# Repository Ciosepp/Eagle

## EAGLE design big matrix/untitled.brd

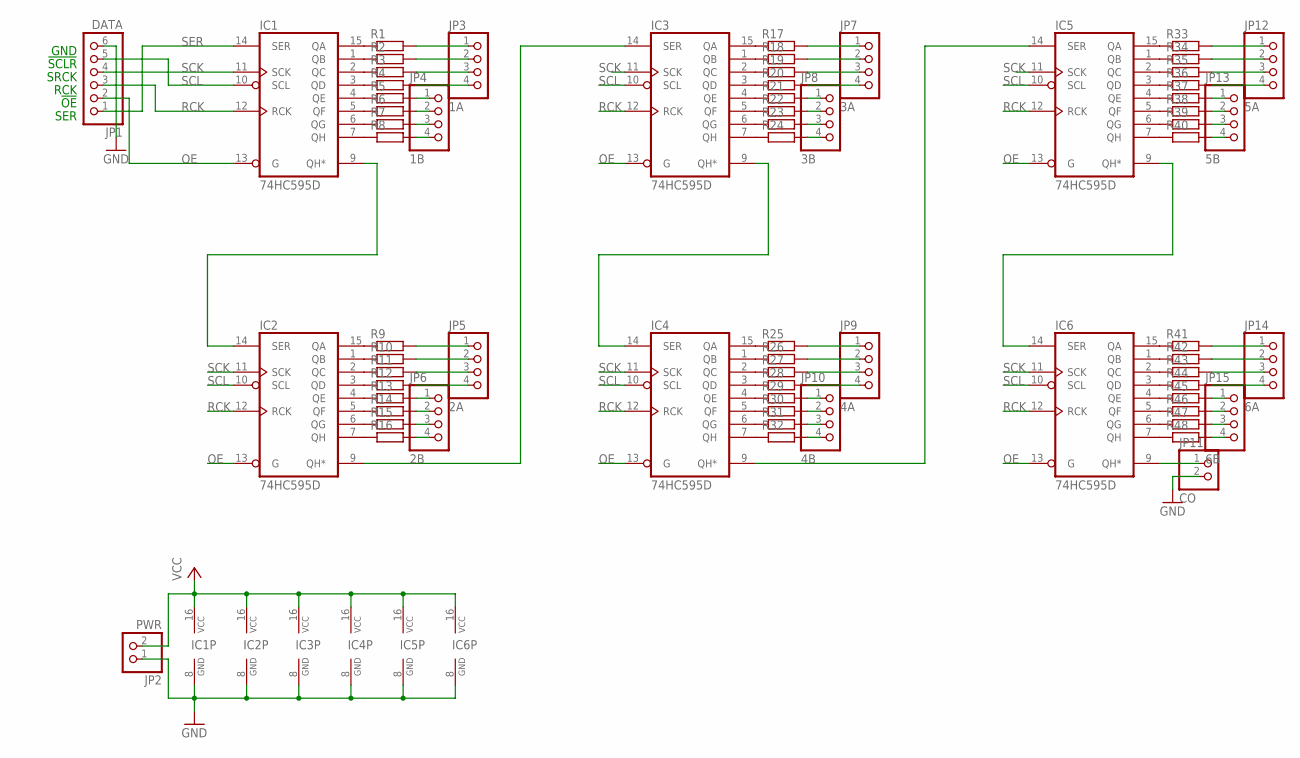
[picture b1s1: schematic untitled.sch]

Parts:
IC1, IC2, IC3, IC4, IC5, IC6: 74HC595D; SO16
JP1: DATA; 1X06
JP2: PWR; 1X02
JP3: 1A; 1X04
JP4: 1B; 1X04
JP5: 2A; 1X04
JP6: 2B; 1X04
JP7: 3A; 1X04
JP8: 3B; 1X04
JP9: 4A; 1X04
JP10: 4B; 1X04
JP11: CO; 1X02
JP12: 5A; 1X04
JP13: 5B; 1X04
JP14: 6A; 1X04
JP15: 6B; 1X04
R1, R2, R3, R4, R5, R6, R7, R8, R9, R10, R11, R12, R13, R14, R15, R16, R17, R18, R19, R20, R21, R22, R23, R24, R25, R26, R27, R28, R29, R30, R31, R32, R33, R34, R35, R36, R37, R38, R39, R40, R41, R42, R43, R44, R45, R46, R47, R48: R-EU_R0805; R0805

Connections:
GND: IC1.8 (GND), IC2.8 (GND), IC3.8 (GND), IC4.8 (GND), IC5.8 (GND), IC6.8 (GND), JP1.6, JP2.1, JP11.2
unnamed: IC2.15 (QA), R9.1
unnamed: IC1.15 (QA), R1.1
unnamed: IC1.1 (QB), R2.1
unnamed: IC1.2 (QC), R3.1
unnamed: IC1.3 (QD), R4.1
unnamed: IC1.4 (QE), R5.1
unnamed: IC1.5 (QF), R6.1
unnamed: IC1.6 (QG), R7.1
unnamed: IC1.7 (QH), R8.1
unnamed: IC2.1 (QB), R10.1
unnamed: IC2.2 (QC), R11.1
unnamed: IC2.3 (QD), R12.1
unnamed: IC2.4 (QE), R13.1
unnamed: IC2.5 (QF), R14.1
unnamed: IC2.6 (QG), R15.1
unnamed: IC2.7 (QH), R16.1
unnamed: JP5.1, R9.2
unnamed: JP5.2, R10.2
unnamed: JP3.1, R1.2
unnamed: JP3.2, R2.2
unnamed: JP3.3, R3.2
unnamed: JP3.4, R4.2
unnamed: JP4.1, R5.2
unnamed: JP4.2, R6.2
unnamed: JP4.3, R7.2
unnamed: JP4.4, R8.2
unnamed: JP5.3, R11.2
unnamed: JP5.4, R12.2
unnamed: JP6.1, R13.2
unnamed: JP6.2, R14.2
unnamed: JP6.3, R15.2
unnamed: JP6.4, R16.2
unnamed: IC1.9 (QH*), IC2.14 (SER)
unnamed: IC3.15 (QA), R17.1
unnamed: IC3.1 (QB), R18.1
unnamed: IC3.2 (QC), R19.1
unnamed: IC3.3 (QD), R20.1
unnamed: IC3.4 (QE), R21.1
unnamed: IC3.5 (QF), R22.1
unnamed: IC3.6 (QG), R23.1
unnamed: IC3.7 (QH), R24.1
unnamed: JP7.1, R17.2
unnamed: JP7.2, R18.2
unnamed: JP7.3, R19.2
unnamed: JP7.4, R20.2
unnamed: JP8.1, R21.2
unnamed: JP8.2, R22.2
unnamed: JP8.3, R23.2
unnamed: JP8.4, R24.2
unnamed: IC4.15 (QA), R25.1
unnamed: IC4.1 (QB), R26.1
unnamed: IC4.2 (QC), R27.1
unnamed: IC4.3 (QD), R28.1
unnamed: IC4.4 (QE), R29.1
unnamed: IC4.5 (QF), R30.1
unnamed: IC4.6 (QG), R31.1
unnamed: IC4.7 (QH), R32.1
unnamed: JP9.1, R25.2
unnamed: JP9.2, R26.2
unnamed: JP9.3, R27.2
unnamed: JP9.4, R28.2
unnamed: JP10.1, R29.2
unnamed: JP10.2, R30.2
unnamed: JP10.3, R31.2
unnamed: JP10.4, R32.2
unnamed: IC3.9 (QH*), IC4.14 (SER)
unnamed: IC2.9 (QH*), IC3.14 (SER)
unnamed: IC6.9 (QH*), JP11.1
unnamed: IC5.15 (QA), R33.1
unnamed: IC5.1 (QB), R34.1
unnamed: IC5.2 (QC), R35.1
unnamed: IC5.3 (QD), R36.1
unnamed: IC5.4 (QE), R37.1
unnamed: IC5.5 (QF), R38.1
unnamed: IC5.6 (QG), R39.1
unnamed: IC5.7 (QH), R40.1
unnamed: JP12.1, R33.2
unnamed: JP12.2, R34.2
unnamed: JP12.3, R35.2
unnamed: JP12.4, R36.2
unnamed: JP13.1, R37.2
unnamed: JP13.2, R38.2
unnamed: JP13.3, R39.2
unnamed: JP13.4, R40.2
unnamed: IC6.15 (QA), R41.1
unnamed: IC6.1 (QB), R42.1
unnamed: IC6.2 (QC), R43.1
unnamed: IC6.3 (QD), R44.1
unnamed: IC6.4 (QE), R45.1
unnamed: IC6.5 (QF), R46.1
unnamed: IC6.6 (QG), R47.1
unnamed: IC6.7 (QH), R48.1
unnamed: JP14.1, R41.2
unnamed: JP14.2, R42.2
unnamed: JP14.3, R43.2
unnamed: JP14.4, R44.2
unnamed: JP15.1, R45.2
unnamed: JP15.2, R46.2
unnamed: JP15.3, R47.2
unnamed: JP15.4, R48.2
unnamed: IC5.9 (QH*), IC6.14 (SER)
unnamed: IC4.9 (QH*), IC5.14 (SER)
OE: IC1.13 (G), IC2.13 (G), IC3.13 (G), IC4.13 (G), IC5.13 (G), IC6.13 (G), JP1.2
RCK: IC1.12 (RCK), IC2.12 (RCK), IC3.12 (RCK), IC4.12 (RCK), IC5.12 (RCK), IC6.12 (RCK), JP1.3
SCK: IC1.11 (SCK), IC2.11 (SCK), IC3.11 (SCK), IC4.11 (SCK), IC5.11 (SCK), IC6.11 (SCK), JP1.4
SCL: IC1.10 (SCL), IC2.10 (SCL), IC3.10 (SCL), IC4.10 (SCL), IC5.10 (SCL), IC6.10 (SCL), JP1.5
SER: IC1.14 (SER), JP1.1
VCC: IC1.16 (VCC), IC2.16 (VCC), IC3.16 (VCC), IC4.16 (VCC), IC5.16 (VCC), IC6.16 (VCC), JP2.2

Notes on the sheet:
SER
!OE
RCK
SRCK
!SCLR
GND

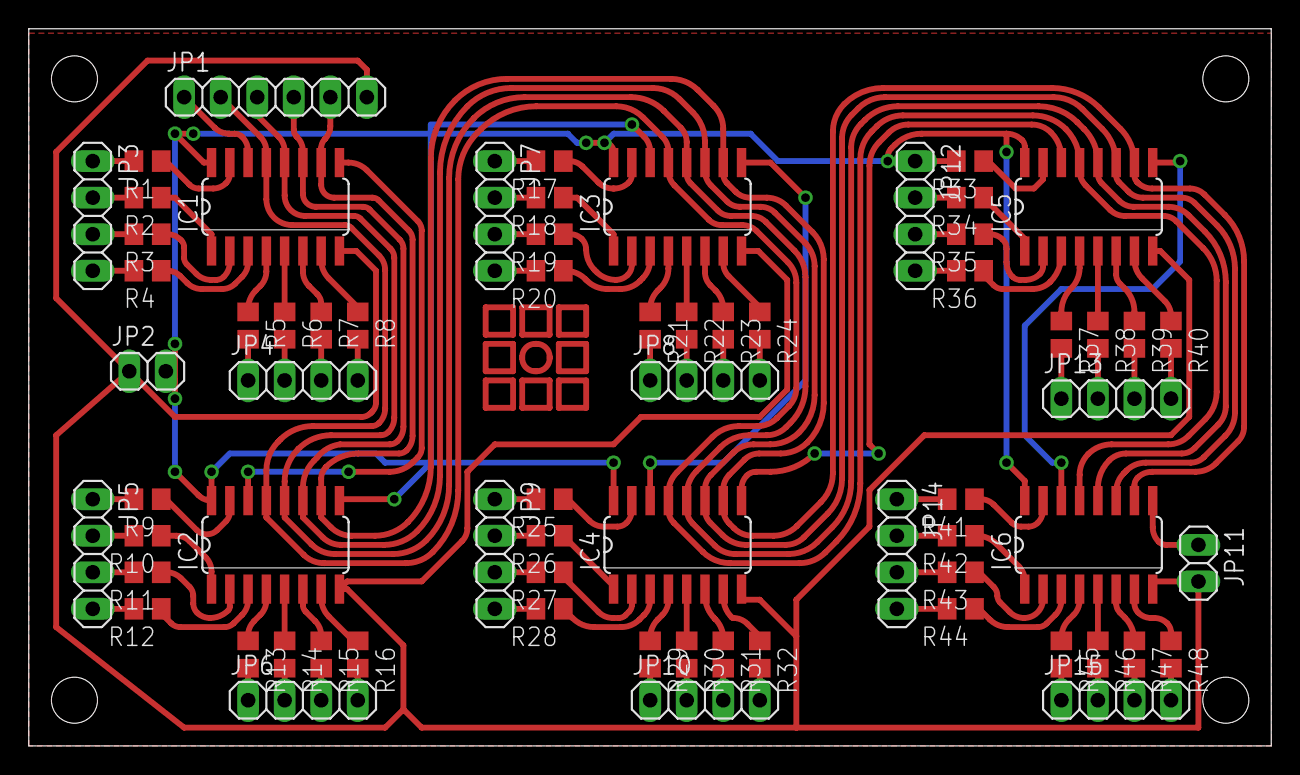
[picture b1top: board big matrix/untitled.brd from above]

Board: 2 copper layers, 86.3 x 49.8 mm, 69 parts (0 on the bottom side), 109 nets.

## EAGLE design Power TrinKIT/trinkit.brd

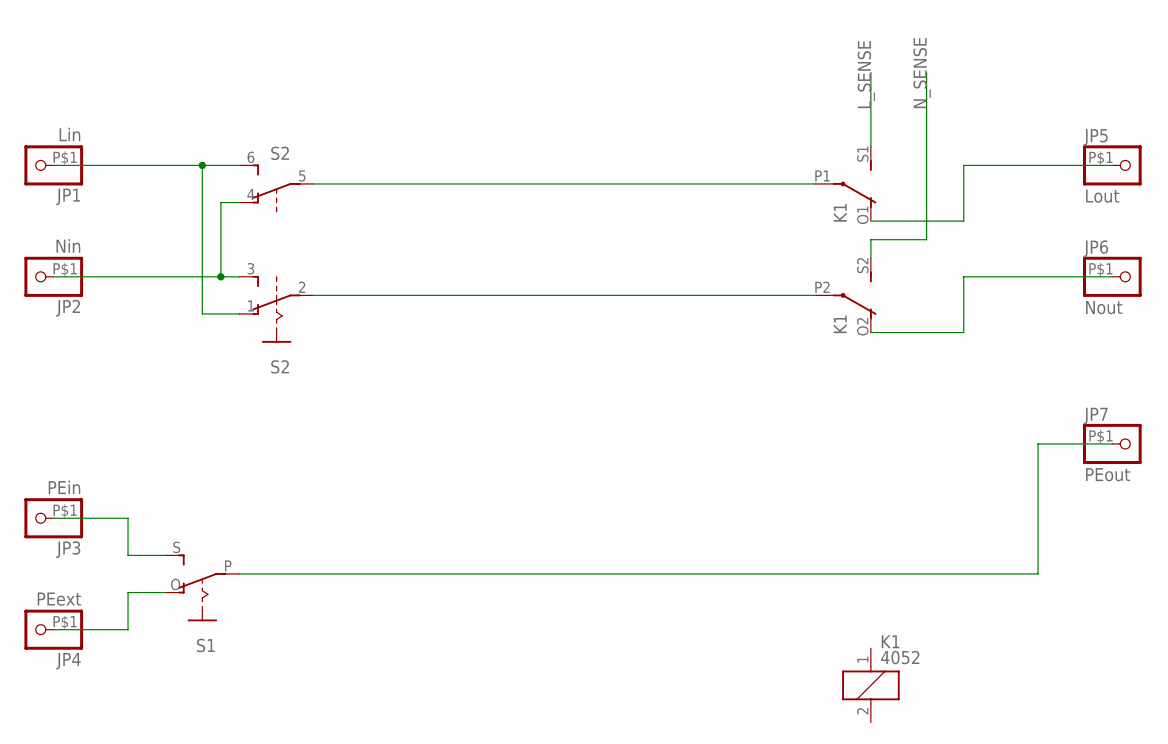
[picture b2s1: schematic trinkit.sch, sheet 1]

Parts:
JP1: Lin; 1X1-BIGPOGO
JP2: Nin; 1X1-BIGPOGO
JP3: PEin; 1X1-BIGPOGO
JP4: PEext; 1X1-BIGPOGO
JP5: Lout; 1X1-BIGPOGO
JP6: Nout; 1X1-BIGPOGO
JP7: PEout; 1X1-BIGPOGO
K1: 4052; F4052
S1: EG1218S; EG1218
S2: A68-A31

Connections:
L_SENSE: K1.S1 (S)
unnamed: K1.P1, S2.5
unnamed: K1.P2, S2.2
unnamed: JP1.P$1, S2.1 (O), S2.6 (S)
unnamed: JP2.P$1, S2.3 (S), S2.4 (O)
unnamed: JP5.P$1, K1.O1 (O)
unnamed: JP6.P$1, K1.O2 (O)
unnamed: JP3.P$1, S1.S
unnamed: JP4.P$1, S1.O
unnamed: JP7.P$1, S1.P
N_SENSE: K1.S2 (S)

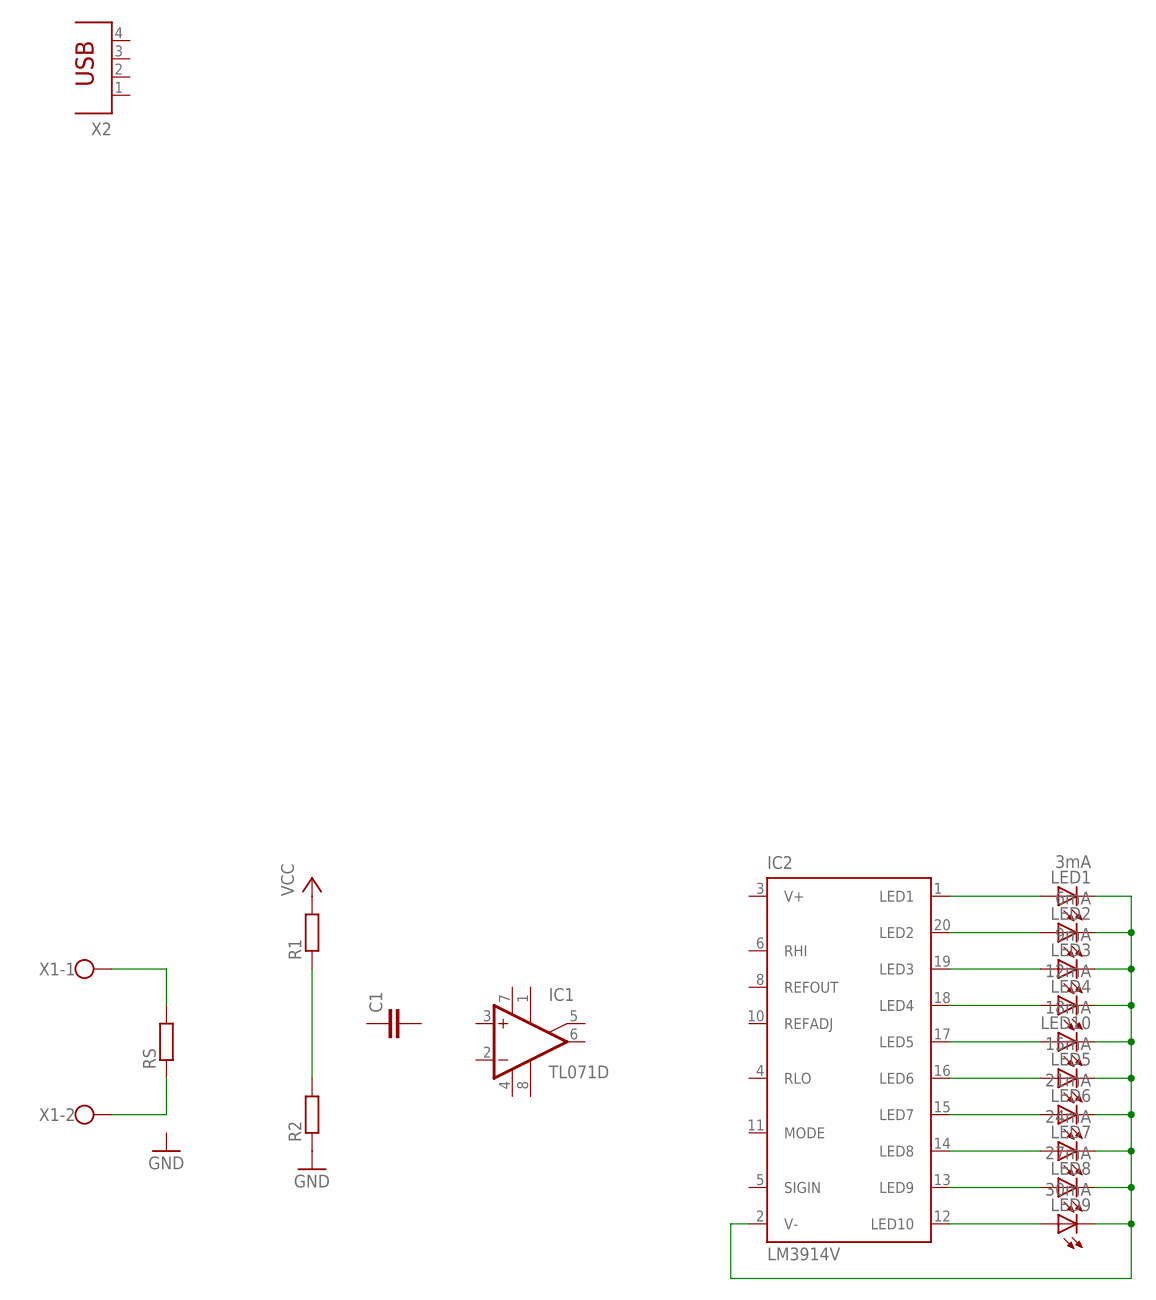
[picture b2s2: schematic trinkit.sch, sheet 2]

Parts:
C1: C-EUC0805; C0805
IC1: TL071D; SO08
IC2: LM3914V; PLCC20S
LED1: 3mA; CHIP-LED0805
LED2: 6mA; CHIP-LED0805
LED3: 9mA; CHIP-LED0805
LED4: 12mA; CHIP-LED0805
LED5: 15mA; CHIP-LED0805
LED6: 21mA; CHIP-LED0805
LED7: 24mA; CHIP-LED0805
LED8: 27mA; CHIP-LED0805
LED9: 30mA; CHIP-LED0805
LED10: 18mA; CHIP-LED0805
R1, R2: R-EU_M0805; M0805
RS: R-EU_M2309; M2309
X1: W237-102
X2: PN87520

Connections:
GND: R2.1
unnamed: IC2.1 (LED1), LED1.A
unnamed: IC2.20 (LED2), LED2.A
unnamed: IC2.19 (LED3), LED3.A
unnamed: IC2.18 (LED4), LED4.A
unnamed: IC2.17 (LED5), LED10.A
unnamed: IC2.16 (LED6), LED5.A
unnamed: IC2.15 (LED7), LED6.A
unnamed: IC2.14 (LED8), LED7.A
unnamed: IC2.13 (LED9), LED8.A
unnamed: IC2.12 (LED10), LED9.A
unnamed: IC2.2 (V-), LED1.C, LED2.C, LED3.C, LED4.C, LED5.C, LED6.C, LED7.C, LED8.C, LED9.C, LED10.C
unnamed: RS.2, X1.1
unnamed: RS.1, X1.2
unnamed: R1.1, R2.2
V+: IC1.7 (V+), IC2.3 (V+)
V-: IC1.4 (V-)
VCC: R1.2

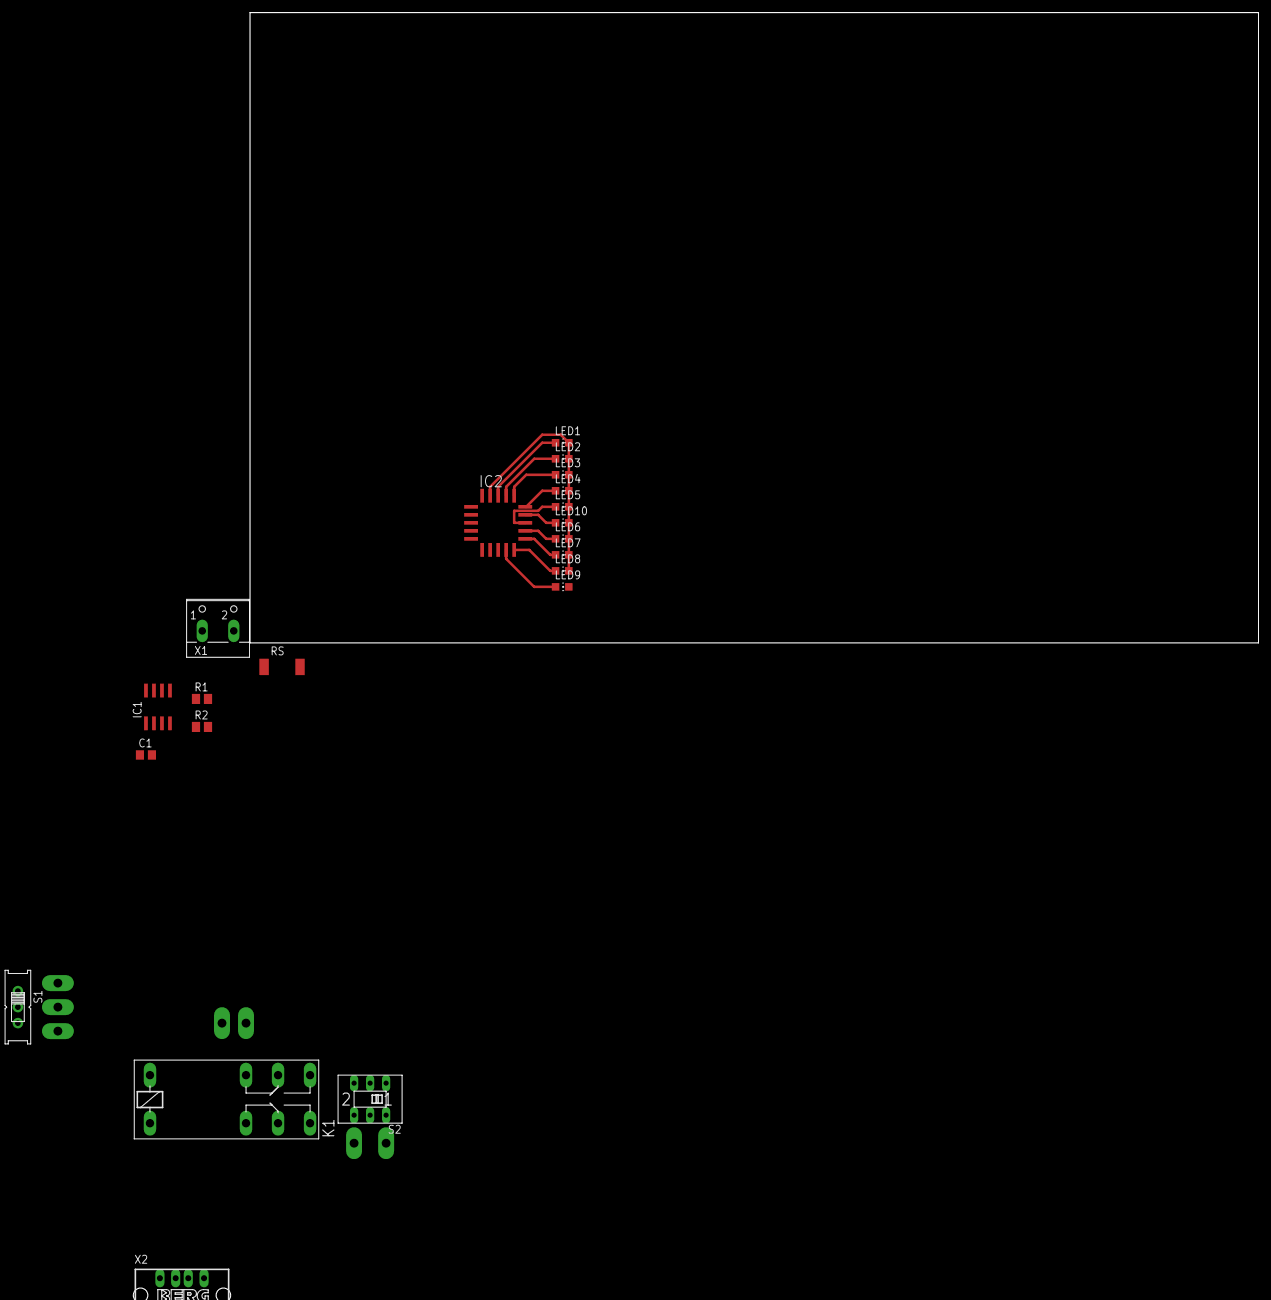
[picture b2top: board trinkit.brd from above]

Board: 2 copper layers, 160.0 x 100.0 mm, 28 parts (0 on the bottom side), 24 nets.

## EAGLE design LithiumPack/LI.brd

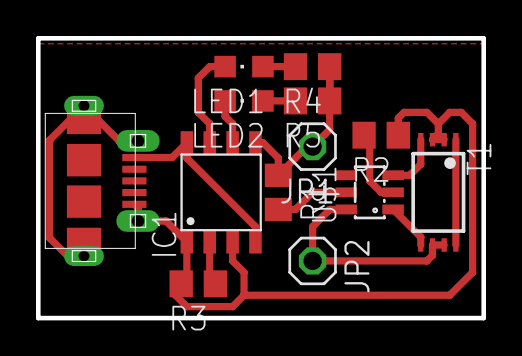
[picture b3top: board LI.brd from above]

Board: 2 copper layers, 24.7 x 15.5 mm, 13 parts (0 on the bottom side), 14 nets.

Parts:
IC1: TP4056; SOP-8
JP1: B+; 1X01
JP2: B-; 1X01
LED1, LED2: CHIPLED_0805
R1: 100; R0805
R2, R4, R5: 1k; R0805
R3: 10k; R0805
T1: DMN3024LSD; TSSOP-8
U$1: DW01A; SOT23-6
U$2: MICRO-USB-RECEPTACLE47589-0001; 47589-0001

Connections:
AGND: IC1.1, IC1.3, R2.1, R3.2, T1.2, T1.3, U$2.5, U$2.CASING1, U$2.CASING2, U$2.CASING3, U$2.CASING4
unnamed: T1.4, U$1.3
unnamed: T1.5, U$1.1
unnamed: T1.1, T1.8
unnamed: R2.2, U$1.2
unnamed: JP2.1, T1.6, T1.7, U$1.6
unnamed: R1.2, U$1.5
unnamed: IC1.2, R3.1
unnamed: LED1.A, R4.2
unnamed: LED2.A, R5.2
unnamed: IC1.7, LED1.C
unnamed: IC1.6, LED2.C
unnamed: IC1.4, IC1.8, U$2.1
VCC: IC1.5, JP1.1, R1.1, R4.1, R5.1

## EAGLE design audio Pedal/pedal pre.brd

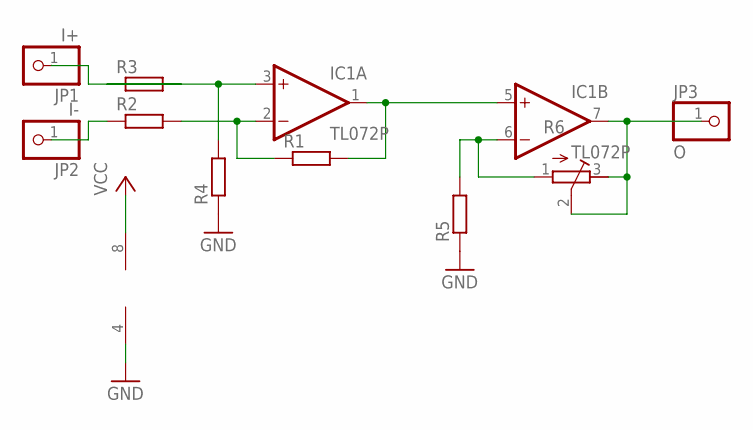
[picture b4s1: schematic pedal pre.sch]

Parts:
IC1: TL072P; DIL08
JP1: I+; 1X01
JP2: I-; 1X01
JP3: O; 1X01
R1, R2, R3, R4, R5: R-EU_0207/2V; 0207/2V
R6: R-TRIMM64W; RTRIM64W

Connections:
GND: IC1.4 (V-), R4.1, R5.1
unnamed: IC1.3 (+IN), R3.1, R4.2
unnamed: IC1.2 (-IN), R1.1, R2.2
unnamed: IC1.1 (OUT), IC1.5 (+IN), R1.2
unnamed: IC1.6 (-IN), R5.2, R6.1 (A)
unnamed: IC1.7 (OUT), JP3.1, R6.2 (S), R6.3 (E)
unnamed: JP1.1, R3.2
unnamed: JP2.1, R2.1
VCC: IC1.8 (V+)

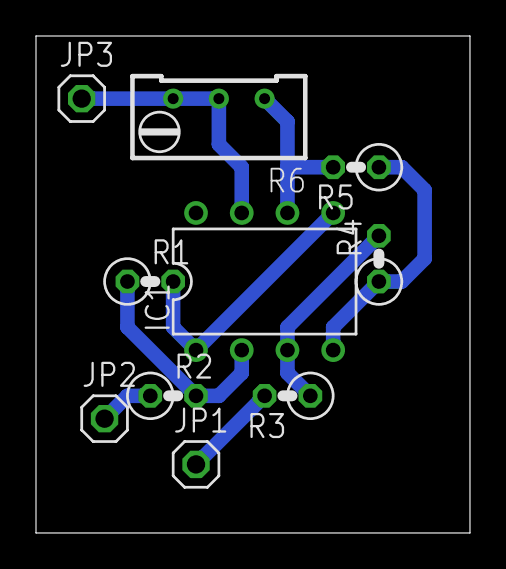
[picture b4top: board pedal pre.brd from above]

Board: 2 copper layers, 24.1 x 27.6 mm, 10 parts (0 on the bottom side), 8 nets.

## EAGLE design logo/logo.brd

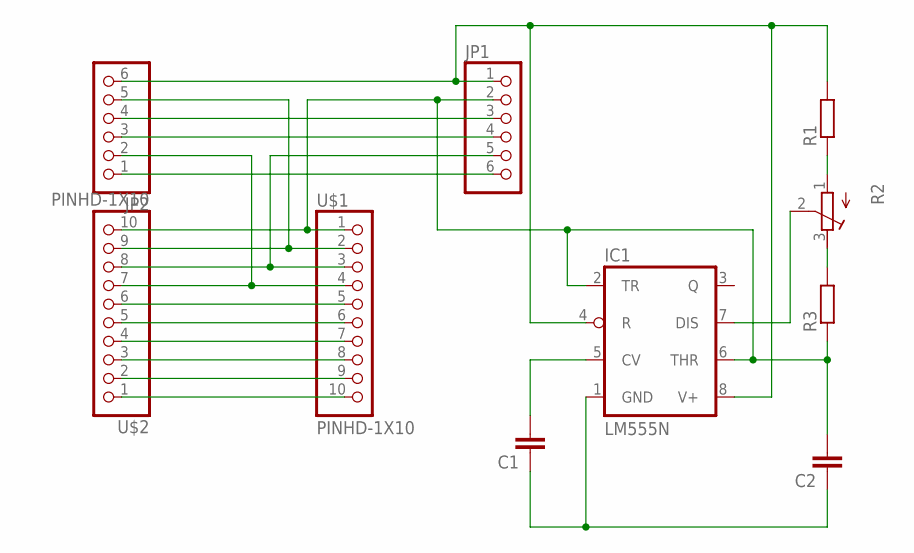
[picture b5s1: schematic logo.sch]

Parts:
C1, C2: C-EU050-025X075; C050-025X075
IC1: LM555N; DIL08-ROUND
JP1, JP2: PINHD-1X6B; 1X06-BIG
R1, R3: R-EU_0204/7; 0204/7
R2: R-TRIMM64W; RTRIM64W
U$1, U$2: PINHD-1X10; 1X10-BIG

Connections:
unnamed: U$1.10, U$2.1
unnamed: U$1.9, U$2.2
unnamed: U$1.8, U$2.3
unnamed: U$1.7, U$2.4
unnamed: U$1.6, U$2.5
unnamed: U$1.5, U$2.6
unnamed: JP2.2, U$1.4, U$2.7
unnamed: JP1.5, U$1.3, U$2.8
unnamed: JP2.5, U$1.2, U$2.9
unnamed: C2.2, IC1.2 (TR), IC1.6 (THR), JP1.2, R3.1, U$1.1, U$2.10
unnamed: JP1.3, JP2.4
unnamed: JP1.4, JP2.3
unnamed: JP1.6, JP2.1
unnamed: IC1.4 (R), IC1.8 (V+), JP1.1, JP2.6, R1.2
unnamed: IC1.7 (DIS), R2.2 (S)
unnamed: R1.1, R2.1 (A)
unnamed: R2.3 (E), R3.2
unnamed: C1.1, C2.1, IC1.1 (GND)
unnamed: C1.2, IC1.5 (CV)

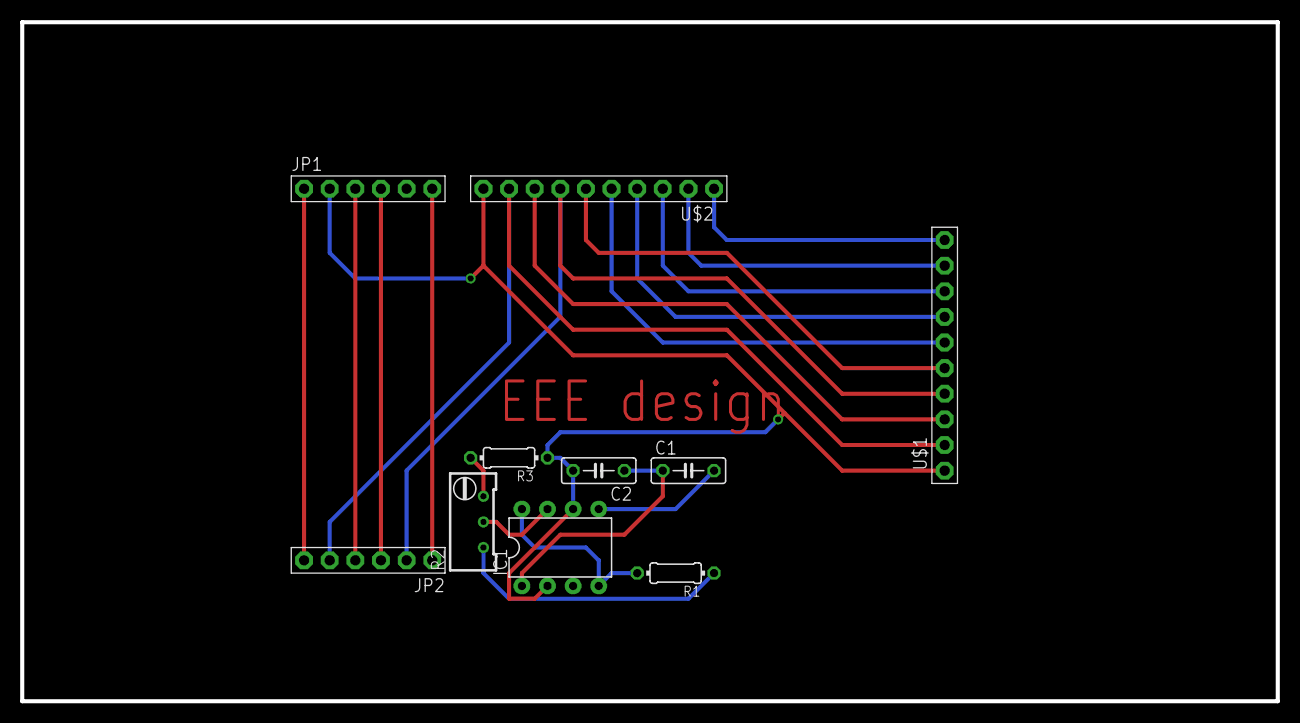
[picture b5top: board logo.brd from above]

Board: 2 copper layers, 124.5 x 67.3 mm, 10 parts (0 on the bottom side), 19 nets.

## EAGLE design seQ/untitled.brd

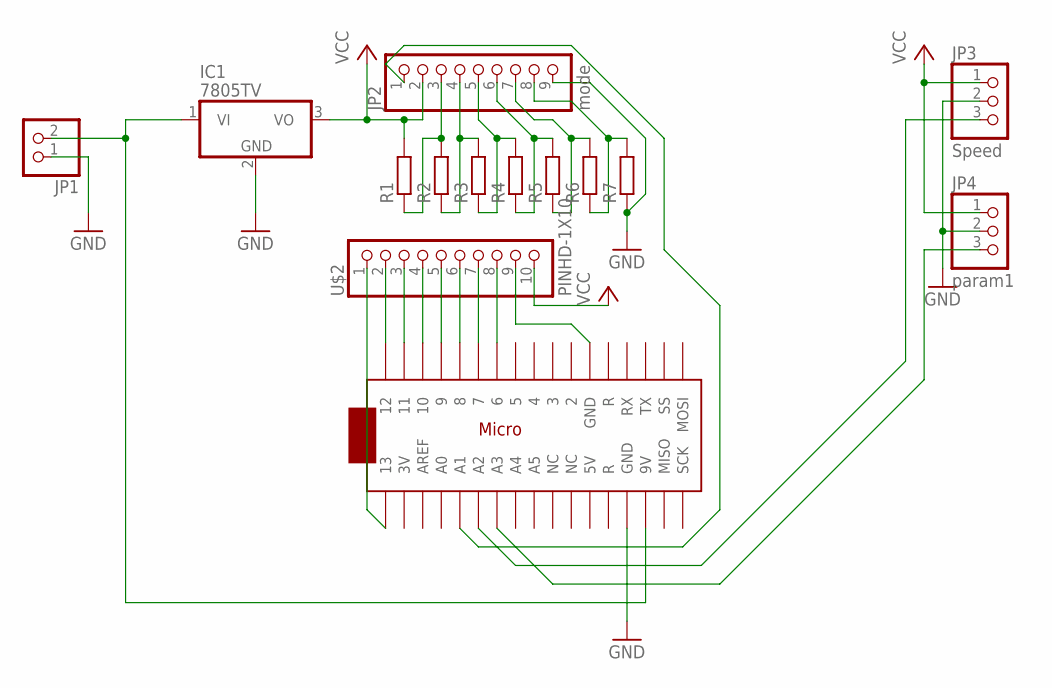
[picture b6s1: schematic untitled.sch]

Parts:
IC1: 7805TV; TO220V
JP1: PINHD-1X2; 1X02
JP2: mode; 1X09-BIG
JP3: Speed; 1X03
JP4: param1; 1X03
R1, R2, R3, R4, R5, R6, R7: R-EU_0204/7; 0204/7
U$1: ARDUINOMICRO
U$2: PINHD-1X10; 1X10-BIG

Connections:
GND: IC1.2 (GND), JP1.1, JP2.9, JP3.2, JP4.2, R7.1, U$1.P$12 (GND)
unnamed: IC1.1 (VI), JP1.2, U$1.P$20 (9V)
unnamed: JP2.3, R1.1, R2.2
unnamed: JP2.4, R2.1, R3.2
unnamed: JP2.5, R3.1, R4.2
unnamed: JP2.6, R4.1, R5.2
unnamed: JP2.7, R5.1, R6.2
unnamed: JP2.8, R6.1, R7.2
unnamed: JP2.1, U$1.P$30 (A1)
unnamed: JP3.3, U$1.P$29 (A2)
unnamed: JP4.3, U$1.P$28 (A3)
unnamed: U$1.P$34 (13), U$2.1
unnamed: U$1.P$1 (12), U$2.2
unnamed: U$1.P$2 (11), U$2.3
unnamed: U$1.P$3 (10), U$2.4
unnamed: U$1.P$4 (9), U$2.5
unnamed: U$1.P$5 (8), U$2.6
unnamed: U$1.P$6 (7), U$2.7
unnamed: U$1.P$7 (6), U$2.8
unnamed: U$1.P$21 (GND), U$2.9
VCC: IC1.3 (VO), JP2.2, JP3.1, JP4.1, R1.2, U$2.10

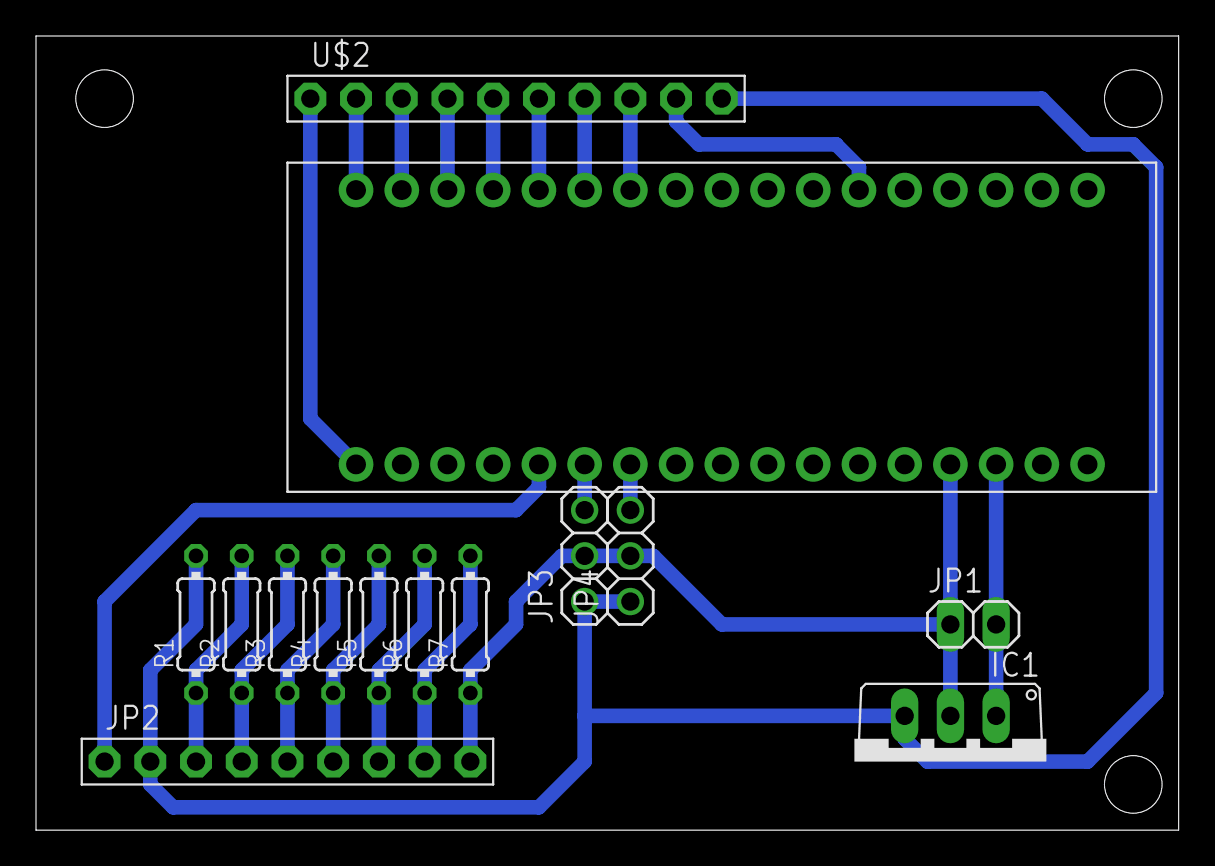
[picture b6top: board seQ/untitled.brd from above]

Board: 2 copper layers, 63.5 x 44.1 mm, 14 parts (0 on the bottom side), 21 nets.

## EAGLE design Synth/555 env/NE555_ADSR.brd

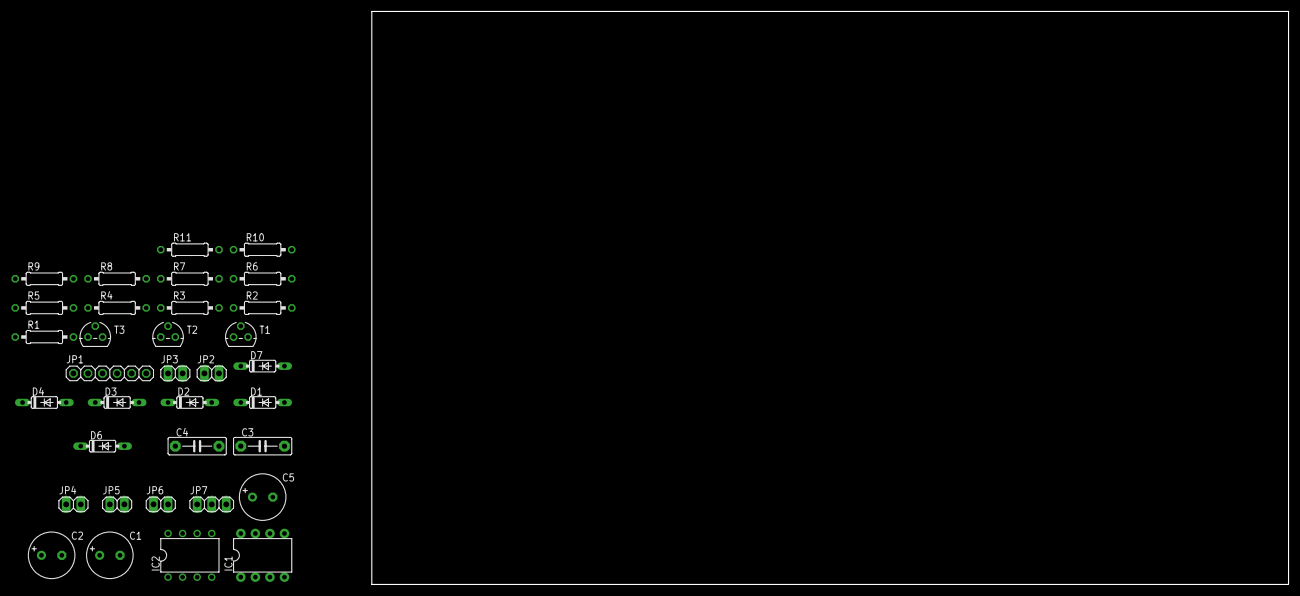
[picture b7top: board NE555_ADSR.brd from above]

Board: 2 copper layers, 160.0 x 100.0 mm, 34 parts (0 on the bottom side), 25 nets, no tracks yet.

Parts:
C1, C2: E3,5-8
C3, C4: 10n; C7.5B3
C5: 4uF; E3,5-8
D1, D2, D3, D4, D7: 1N4148; DO35-7
D6: 1N4148DO35-7; DO35-7
IC1: NE555N; DIL08-ROUND
IC2: TL082P; DIL08
JP1: 1X06
JP2, JP3: 1X02
JP4: 2M2_A; 1X02
JP5: 2M2_R; 1X02
JP6: 2M2_D; 1X02
JP7: 10k_S; 1X03
R1, R4, R5: 4k7; 0207/10
R2, R6: 10k; 0207/10
R3: 22k; 0207/10
R7, R9, R10: 0207/10
R8: 220; 0207/10
R11: 3.3k; 0207/10
T1, T2, T3: 2N3904; TO92

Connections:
A: D7.A, IC1.3
GND: C1.-, C2.+, C4.2, C5.-, D1.A, D6.A, IC1.1, IC2.8, JP1.3, JP1.4, JP2.1, T1.3, T2.3, T3.3
unnamed: R6.1, T3.2
unnamed: JP2.2, R2.2
unnamed: JP4.2, R8.2
unnamed: C4.1, IC1.5
unnamed: R1.1, R3.1, T1.1
unnamed: D3.C, JP7.2
unnamed: IC1.2, R5.1, T3.1
unnamed: D6.C, R2.1, R7.1, T1.2
unnamed: C3.2, D1.C, R6.2
unnamed: R3.2, T2.2
unnamed: D7.C, R8.1
unnamed: IC2.1, IC2.2, JP3.1
unnamed: JP5.2, R9.2
unnamed: JP6.2, R10.2
unnamed: D3.A, R10.1
unnamed: D2.A, R9.1
unnamed: JP7.1, R11.1
unnamed: D4.C, IC1.4
unnamed: C5.+, IC1.6, IC2.3, JP4.1, JP5.1, JP6.1
R: C3.1, D2.C, D4.A, R4.1, R7.2, T2.1
S: IC1.7, JP7.3
VCC: C1.+, IC1.8, IC2.4, JP1.5, JP1.6, R1.2, R4.2, R5.2, R11.2
VDD: C2.-, JP1.1, JP1.2

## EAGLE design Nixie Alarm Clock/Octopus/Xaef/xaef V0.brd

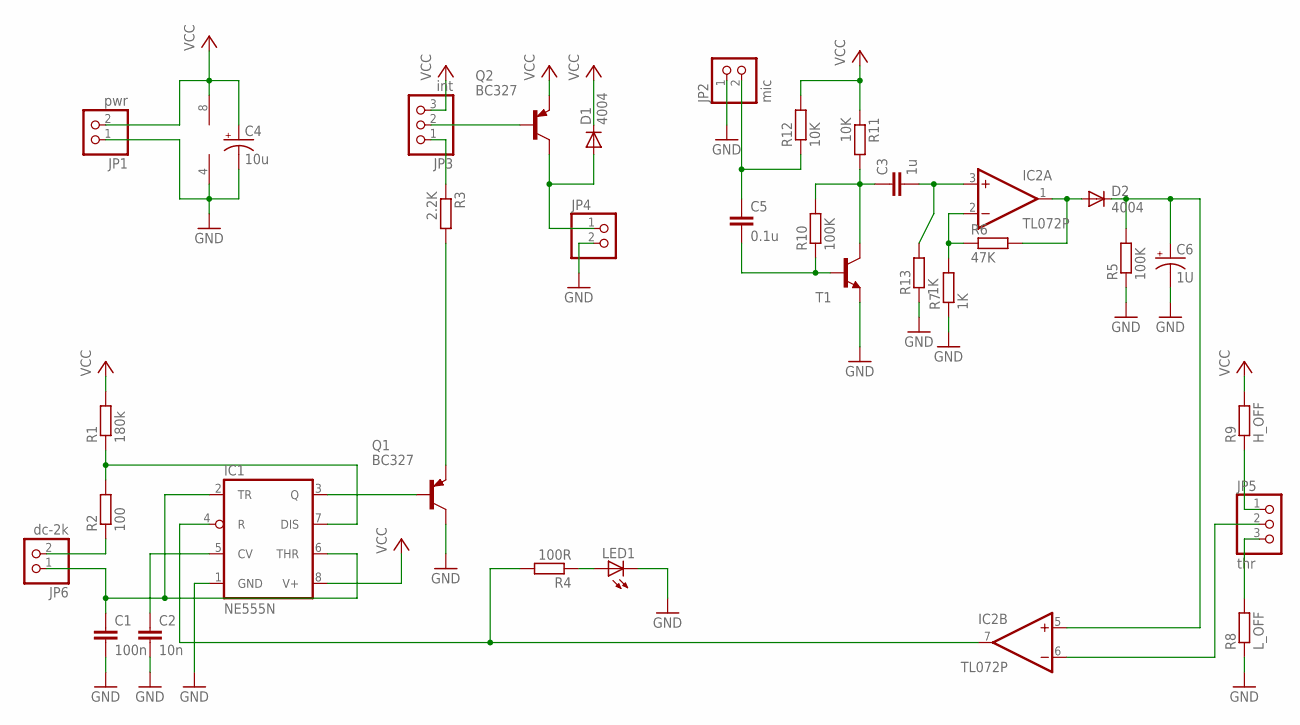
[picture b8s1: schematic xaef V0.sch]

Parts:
C1: 100n; C050-030X075
C2: 10n; C050-030X075
C3: 1u; C050-030X075
C4: 10u; E3,5-8
C5: 0.1u; C050-025X075
C6: 1U; E3,5-8
D1, D2: 4004; D-2.5
IC1: NE555N; DIL08-ROUND
IC2: TL072P; DIL08
JP1: pwr; 1X02
JP2: mic; 1X02
JP3: int; 1X03
JP4: PINHD-1X2; 1X02
JP5: thr; 1X03
JP6: dc-2k; 1X02
LED1: LED5MM
Q1, Q2: BC327; TO92-EBC
R1: 180k; 0207/2V
R2: 100; 0207/2V
R3: 2.2K; 0207/2V
R4: 100R; 0207/2V
R5, R10: 100K; 0207/2V
R6: 47K; 0207/2V
R7, R13: 1K; 0207/2V
R8: L_OFF; 0207/2V
R9: H_OFF; 0207/2V
R11, R12: 10K; 0207/2V
T1: 2N3904-NPN-TO92-EBC; TO92-EBC

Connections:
GND: C1.2, C2.2, C4.-, C6.-, IC1.1 (GND), IC2.4 (V-), JP1.1, JP2.1, JP4.2, LED1.K (C), Q1.C, R5.1, R7.1, R8.1, R13.1, T1.E
unnamed: IC1.7 (DIS), R1.1, R2.2
unnamed: IC1.3 (Q), Q1.B
unnamed: JP3.2, Q2.B
unnamed: Q1.E, R3.2
unnamed: D1.A, JP4.1, Q2.C
unnamed: C2.1, IC1.5 (CV)
unnamed: C1.1, IC1.2 (TR), IC1.6 (THR), JP6.1
unnamed: LED1.A, R4.1
unnamed: IC1.4 (R), IC2.7 (OUT), R4.2
unnamed: JP3.1, R3.1
unnamed: IC2.2 (-IN), R6.1, R7.2
unnamed: JP6.2, R2.1
unnamed: D2.A, IC2.1 (OUT), R6.2
unnamed: C3.2, IC2.3 (+IN), R13.2
unnamed: C3.1, R10.2, R11.2, T1.C
unnamed: JP5.3, R8.2
unnamed: JP5.1, R9.1
unnamed: C5.2, R10.1, T1.B
unnamed: IC2.6 (-IN), JP5.2
unnamed: C6.+, D2.C, IC2.5 (+IN), R5.2
unnamed: C5.1, JP2.2, R12.1
VCC: C4.+, D1.C, IC1.8 (V+), IC2.8 (V+), JP1.2, JP3.3, Q2.E, R1.2, R9.2, R11.1, R12.2

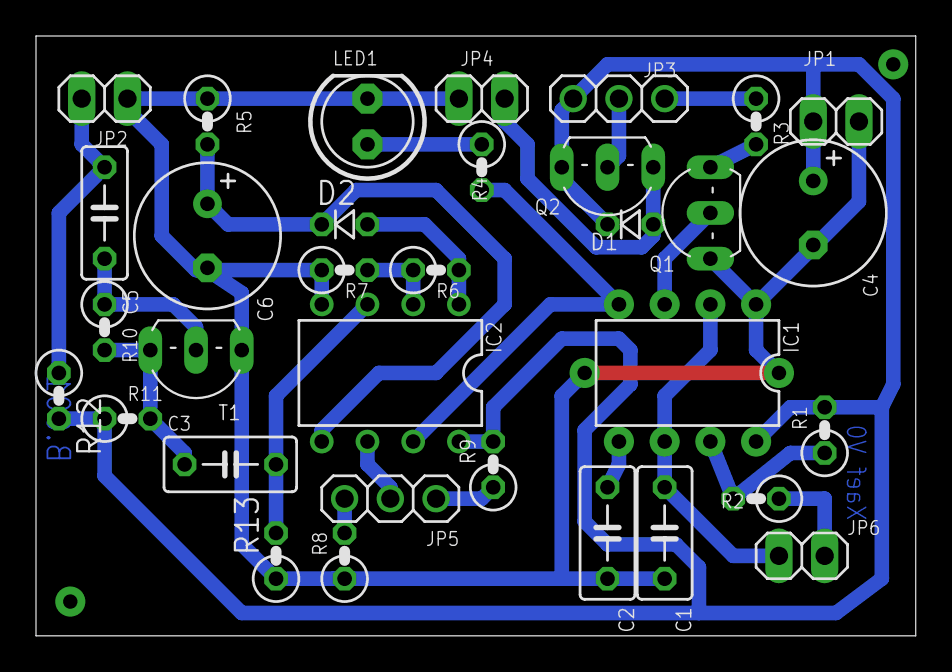
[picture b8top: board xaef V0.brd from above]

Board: 2 copper layers, 48.9 x 33.3 mm, 33 parts (0 on the bottom side), 23 nets.

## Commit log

2021-03-12 First
2021-03-29 29/03/21 update
2021-04-07 Created and added partlist
2022-07-17 just a sync

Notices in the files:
parts and their libraries:
con-molex-usb: (C) 2014 Tomasz Boleslaw CEDRO, cederom@tlen.pl, http://www.tomek.cedro.info.
